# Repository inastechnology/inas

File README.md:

# INAS

Japanese documentation: [docs/jp/README.md](docs/jp/README.md)

INAS is an agriculture platform for observing field conditions, operating
irrigation equipment, managing device settings and firmware, and recording the
results of farm work. This monorepo contains the complete platform: ESP32-S3
device firmware, the Local Hub, the field-side Edge Gateway, the shared Cloud
Hub, common contracts, extensions, and user documentation.

The system is designed to keep MQTT communication and safety-critical device
operation on the field LAN. A site can operate devices directly from a Local
Hub or use an Edge Gateway that synchronizes with one parent Local Hub or Cloud
Hub over outbound HTTPS.

Start with [INAS System Specification](docs/SYSTEM_SPECIFICATION.md) for the cross-project
architecture, device roles, field data model, OTA flow, and Cloudflare hosted
options. The draw.io source for the system diagrams is
[docs/assets/inas_system_diagrams.drawio](docs/assets/inas_system_diagrams.drawio).
Documentation writing and localization rules are defined in
[docs/DOCUMENTATION_GUIDE.md](docs/DOCUMENTATION_GUIDE.md).
System-wide layer boundaries are defined in
[docs/ARCHITECTURE_LAYERING_POLICY.md](docs/ARCHITECTURE_LAYERING_POLICY.md).
Planned and community-proposed work is indexed in
[docs/FUTURE_FEATURES.md](docs/FUTURE_FEATURES.md).
Japanese documentation is stored under documentation directories such as
[docs/jp/README.md](docs/jp/README.md), [hub/doc/jp/README.md](hub/doc/jp/README.md),
and [client-devices/docs/jp/README.md](client-devices/docs/jp/README.md).

## System overview

```text
INAS devices -- MQTT --> Local Hub

INAS devices -- MQTT --> Edge Gateway -- Sync v1 HTTPS --> Local Hub or Cloud Hub
```

The Hub combines device status, measurements, irrigation history, field and
crop context, work records, Runtime Config, and OTA updates in one operator
interface. See the
[INAS System Specification](docs/SYSTEM_SPECIFICATION.md) for the complete
architecture, data flow, device roles, storage boundaries, and current feature
scope.

## Repository layout

| Path | Purpose |
|---|---|
| [`hub/`](hub/README.md) | Local Hub: Flask UI/API, MQTT processing, scheduling, storage integration, and OTA delivery |
| [`hub-cloud/`](hub-cloud/README.md) | Shared Cloudflare Workers Cloud Hub with authenticated tenant routing and one database per customer |
| [`edge-gateway/`](edge-gateway/README.md) | Field appliance: local MQTT broker integration, configuration cache, durable outbox, and parent synchronization |
| [`client-devices/`](client-devices/README.md) | PlatformIO firmware for WTR, WRS, FGT, SOI, and ENV devices, plus the shared firmware library |
| [`shared/`](shared/README.md) | Language-neutral Sync contracts and the Python edge runtime shared by the Hub and Gateway |
| [`extensions/`](extensions/README.md) | Declarative, build-time Hub UI extensions |
| [`docs-site/`](docs-site/README.md) | Japanese-first public setup, operation, and troubleshooting website |
| [`docs/`](docs/README.md) | Cross-project specifications, architecture policies, and editable system diagrams |
| [`lp/`](lp/README.md) | Product landing page and its deployable assets |
| [`pitch-deck/`](pitch-deck/) | Product presentation sources and generated artifacts |

## Installation and first run

This is a multi-component repository; there is no repository-wide installer.
Install dependencies from the directory of the component you intend to run.

### Prerequisites

- Git
- Python 3.11 or later and
  [uv](https://docs.astral.sh/uv/getting-started/installation/) for the Local
  Hub, Edge Gateway, and shared Python runtime
- Node.js 22 and npm for the Cloud Hub, admin UI, documentation site, and
  product web assets
- Linux or WSL2, GNU Make, and PlatformIO for client firmware builds

Client firmware uses symbolic links for local PlatformIO libraries. Native
Windows firmware builds are not supported; use WSL2 and clone the repository
inside the Linux filesystem rather than under `/mnt/c`.

### Clone the repository

```bash
git clone https://github.com/inastechnology/inas.git
cd inas
```

### Run the Local Hub

```bash
cd hub
uv sync
uv run ina-hub install
uv run python src/ina_device_hub/serve.py
```

The default local URL is `http://localhost:39151`. The installation command
creates the Hub environment configuration interactively. MQTT, database,
object storage, Cloudflare, and production service settings are documented in
the [Hub README](hub/README.md) and
[Hub operations documentation](hub/doc/OPERATIONS.md).

### Build client firmware

The following example builds the WTR watering device:

```bash
cd client-devices/watering-device
cp default.env.user.ini .env.user.ini
make build
```

Run `make upload` to flash a connected development device or
`make merged-bin` to produce a distributable image. Hardware preparation,
wiring, per-device build targets, and manufacturing steps are indexed from the
[client device documentation](client-devices/README.md).

### Start another component

| Goal | Initial dependency command | Detailed guide |
|---|---|---|
| Develop the Edge Gateway | `cd edge-gateway && uv sync --frozen` | [Edge Gateway README](edge-gateway/README.md) |
| Develop or test the Cloud Hub | `cd hub-cloud && npm ci` | [Cloud Hub README](hub-cloud/README.md) |
| Preview the public documentation | `cd docs-site && npm ci && npm run dev` | [Documentation site README](docs-site/README.md) |
| Build the Hub admin UI | `cd hub/admin-ui && npm ci && npm run build` | [Hub README](hub/README.md) |

## Documentation

For installation, configuration, daily operation, firmware updates, and
troubleshooting, start with the task-oriented
[INAS user documentation](https://docs.inas-technologies.com/). Its source and
local preview instructions are in [`docs-site/`](docs-site/README.md).

Developers should use these entry points instead of adding implementation
details to this README:

- [System specification](docs/SYSTEM_SPECIFICATION.md)
- [Architecture layering policy](docs/ARCHITECTURE_LAYERING_POLICY.md)
- [Device Definition specification](docs/DEVICE_DEFINITION_SPECIFICATION.md)
- [Hub Extension specification](docs/EXTENSION_SPECIFICATION.md)
- [Edge Gateway hardware and identity](docs/EDGE_GATEWAY_HARDWARE_AND_IDENTITY.md)
- [Documentation index](docs/README.md)

Each component owns its dependencies, environment variables, tests, deployment
procedures, and security notes. Run commands from that component's directory
and follow its README before changing or deploying it. Never commit real
database tokens, MQTT credentials, Cloudflare secrets, device credentials, or
generated production configuration.

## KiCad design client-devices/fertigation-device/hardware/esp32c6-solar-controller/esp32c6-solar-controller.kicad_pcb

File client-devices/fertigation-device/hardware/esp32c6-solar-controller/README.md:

# FGT ESP32-C6 Solar Controller

Status: **development CAD only — not fabricated and not used by the current
FGT hardware**.

This directory contains an in-progress candidate design for a future dedicated
controller PCB. A physical board based on this design does not currently exist,
has not been assembled or electrically validated, and must not be treated as
the current FGT wiring or firmware pin contract. Generated ERC/DRC, Gerber,
BOM, CPL, and enclosure outputs show CAD consistency only; they are not evidence
of a manufactured or working device.

The current FGT firmware bring-up uses the direct-wired XIAO ESP32-C6 pin
contract in
[`../../docs/jp/minimal_wiring.md`](../../docs/jp/minimal_wiring.md).

## Design documents

- [BOM index](BOM_DRAFT.md)
- [Rev A 試作発注・組立ガイド](ORDERING.md)
- [主要部品の選定結果](PART_SELECTION.md) — 採用MPN、LCSC番号、定格根拠、
  ヒューズとコネクタの組み合わせ、発注前確認条件
- [部品仕様調査](COMPONENT_SPECIFICATIONS.md) — メーカー一次資料に基づく
  採用部品ごとの電気仕様、pinout、回路上の使用条件
- [Rev A 電気設計DR](ELECTRICAL_DESIGN_REVIEW.md) — 仕様照合結果、回路計算、
  今回の修正、試作後に必要な安全・熱・負荷試験
- [Electrical BOM](ELECTRICAL_BOM.md) — PCB実装部品、電源、RS485、
  MOSFET出力回路、基板上コネクタ
- [Electrical procurement worksheet](ELECTRICAL_PROCUREMENT.csv) —
  主要電子部品の仕様、メーカー型番、LCSC番号、一次資料、実装区分
- [Enclosure and assembly BOM](ENCLOSURE_BOM.md) — 防水筐体、外部コネクタ、
  ハーネス、取付金具、ラベル、シール材
- [Hydraulic and field BOM](HYDRAULIC_AND_FIELD_BOM.md) — 液肥タンク、
  ポンプ、配管、液面・漏水検知、水中コネクタの適用条件
- [Hydraulic procurement worksheet](HYDRAULIC_AND_FIELD_PROCUREMENT.csv) —
  メーカー、型番、購入先URL、単価、発注数の記入用CSV

## KiCad development design

Open [esp32c6-solar-controller.kicad_pro](esp32c6-solar-controller.kicad_pro)
with KiCad 10. The project contains the Rev A single-sheet A1 schematic and routed
`180 x 115 mm` four-layer PCB:

- 20 A shared 12 V input path with LM74610-Q1 reverse-polarity control;
- XIAO ESP32-C6 direct-GPIO control section;
- one board-mounted THVD1410DR RS485 interface with termination and TVS;
- PTC-protected 12 V field power and three generic parallel RS485 connectors;
- normally-closed leak and emergency-stop safety inputs;
- reset-safe hardware gate permission; and
- five individually fused low-side MOSFET output channels.

Related project files:

- [KiCad schematic](esp32c6-solar-controller.kicad_sch)
- [Local symbol library](INA.kicad_sym)
- [XIAO 24-pad SMD footprint](INA_ESP32C6.pretty/XIAO_ESP32C6_SMD_24P.kicad_mod)
- [Schematic PDF](exports/esp32c6-solar-controller.pdf)
- [Schematic layout preview](exports/review/schematic-a1-layout.png)
- [PCB top render](exports/review/pcb-top.png)
- [PCB isometric render](exports/review/pcb-isometric.png)
- [JLCPCB Gerber ZIP](exports/esp32c6-solar-controller-rev-a-gerbers.zip)
- [JLCPCB SMT BOM](exports/assembly/jlcpcb-smt-bom.csv)
- [JLCPCB SMT CPL](exports/assembly/jlcpcb-smt-cpl.csv)
- [Post-assembly BOM](exports/assembly/post-assembly-bom.csv)
- [Board-only STEP](exports/mechanical/controller-board-only-rev-a.step)
- [Final ERC](exports/erc-final.json)
- [Final DRC](exports/drc-final.json)
- [Connectivity netlist](exports/esp32c6-solar-controller.net.xml)

The schematic, local libraries, and release outputs are reproducible with:

```bash
python3 tools/generate_schematic.py
tools/export_release.sh
```

Running the generator overwrites the generated KiCad schematic, project,
symbol library, and XIAO footprint. Do not make GUI-only schematic edits and
then rerun the generator without first carrying those changes back into the
generator.

Validation status:

- opened and exported with KiCad CLI 10.0.5;
- ERC: zero errors and zero warnings;
- PCB DRC: zero violations and zero unconnected items;
- 121 schematic components and 72 named nets;
- 125 PCB footprints including four mounting holes and 72 PCB nets;
- 90 JLCPCB top-side SMT placements, 23 post-assembly parts, and 8 explicit
  DNP parts;
- every populated SMT part has MPN, footprint, and LCSC number; and
- PDF, Gerber, drill, BOM/CPL, assembly, DXF, SVG, and STEP exports generated.

The project-local symbols currently use passive electrical pin types. ERC
therefore verifies file integrity, grid placement, named connectivity,
unconnected-pin declarations, and library consistency, but it does not replace
an electrical review of driver direction, power-source conflicts, current
ratings, or fail-safe behavior.

Major active parts, power semiconductors, fuses, connector families, and
manufacturer land patterns are fixed in [PART_SELECTION.md](PART_SELECTION.md).
JLCPCB/LCSC stock, placement rotation, and package data are still checked in the
order preview. Charger voltage, actual motor inrush, enclosure temperature, and
field wiring are commissioning limits rather than reasons to leave the PCB
undefined.

## Product boundary

This CAD is a candidate future `FGT` hardware profile for a solar-powered
fertilizer mixing and irrigation controller. It is not the current prototype
hardware profile. If developed further, it is intended to keep the existing
FGT state machine, Runtime Config, status contract, and safety invariants while
using a directly soldered Seeed Studio XIAO ESP32-C6.
The module uses the official 24-pad SMD land pattern so its four underside GPIO
pads are available. The XIAO is consequently a reflow/hot-air service part
rather than a socket-replaceable module.

The physical board exposes five generic MOSFET outputs, one RS485 bus on three
parallel terminals, one flow-pulse input, and four contact inputs. The current
FGT Runtime Config maps those generic resources to:

- clean-water inlet valve or transfer pump;
- A concentrate dosing pump;
- B concentrate dosing pump;
- mixing/circulation pump;
- irrigation pump;
- inlet flow pulse;
- tank-empty and tank-full switches;
- leak and emergency-stop inputs; and
- RS485 devices selected for each installation.

No soil, PAR, or other sensor type is fixed in the PCB, connector name, or
electrical BOM. Device model, Modbus address, register map, and meaning belong
to deployment configuration and firmware/device-definition data.

The solar charger, battery BMS, main fuse, and battery disconnect are external
assemblies. The first enclosure may hold the off-board solar controller and
provide separate two-pin panel connectors for the solar panel and battery. The
controller PCB receives power only from the solar controller's protected load
output. This PCB does not charge an unknown battery chemistry.

## Prototype architecture

```text
solar panel -- 2-pin panel connector --+
                                        |
                                off-board solar controller
                                        |
battery ----- 2-pin panel connector ----+
                                        |
                                 protected LOAD output
                                        |
    +-- protected board input -----------------------------+
    |                                                      |
    +-- 12 V actuator distribution (optional 5V_ACT)       |
                                                           |
                              +----------------------------+
                              |
                     reverse-polarity protection
                              |
                +-------------+-------------------+
                |                                 |
           5 V logic buck                 PTC-protected 12 V field rail
                |                                 |
        XIAO ESP32-C6 direct GPIO         generic RS485 ports 1 / 2 / 3
                |
        safety-gated driver enables
                |
       five replaceable actuator drivers
```

The controller board repeats one safety-gated MOSFET channel per actuator.
Power-SMT MOSFETs, gate drivers, fuses, suppression devices, and connectors are
selected only after the real load voltage, running current, stall current, and
inrush measurements are approved. Revision 1 keeps each power channel
independently fused and testable instead of hiding it in a sealed power module.

## XIAO ESP32-C6 pin contract

| Function | XIAO pad | ESP32-C6 GPIO | Reset/safety rule |
|---|---|---:|---|
| Battery voltage ADC | `D0` / pad 1 | `GPIO0` | High-impedance divider; never exceed 3.3 V |
| Output command 1 | `D1` / pad 2 | `GPIO1` | External 47 kohm pull-down; boot default OFF |
| Inlet flow pulse | `D2` / pad 3 | `GPIO2` | Filtered input with defined pull state |
| Actuator master enable | `D3` / pad 4 | `GPIO21` | External pull-down; LOW disables all outputs |
| Output command 2 | `D4` / pad 5 | `GPIO22` | External 47 kohm pull-down; boot default OFF |
| Output command 3 | `D5` / pad 6 | `GPIO23` | External 47 kohm pull-down; boot default OFF |
| RS485 TX | `D6` / pad 7 | `GPIO16` | Direct 3.3 V UART connection |
| RS485 RX | `D7` / pad 8 | `GPIO17` | 3.3 V logic only |
| RS485 DE/RE | `D8` / pad 9 | `GPIO19` | External pull-down selects receive mode |
| Tank empty | `D9` / pad 10 | `GPIO20` | Filtered active-low input |
| Tank full | `D10` / pad 11 | `GPIO18` | Filtered active-low input |
| Output command 4 | `MTDI` / pad 15 | `GPIO5` | Strap pin held LOW by 47 kohm output pull-down |
| Leak status | `MTDO` / pad 16 | `GPIO7` | Filtered status input; hardware also removes permission |
| Output command 5 | `MTMS` / pad 19 | `GPIO4` | Strap pin held LOW by 47 kohm output pull-down |
| Emergency-stop status | `MTCK` / pad 20 | `GPIO6` | Filtered status input; hardware also removes permission |

The XIAO USB-C connector, BOOT button, and RESET button remain accessible after
installation. The XIAO antenna end must be located at a board and enclosure
edge, with no copper, battery, pump, cable bundle, or metal hardware in its
antenna keep-out region.

`GPIO4` and `GPIO5` are ESP32-C6 strapping pins sampled during reset. They are
used only for output commands because each one has a physical 47 kohm
pull-down, producing the required OFF/LOW boot state. They must never receive
an external pull-up. Production validation must include cold boot, reset, USB
download, and OTA restart tests with all five gates verified OFF.

The five direct commands retain the FGT default order: clean-water inlet,
A concentrate, B concentrate, mixer, and irrigation. They reach the gate
drivers only when the independent master-enable safety chain is valid.

Leak and emergency stop must also remove actuator permission in hardware. The
firmware reads and reports the same signals directly, but a crashed MCU or
incorrect output command cannot override the hardware disable.

This PCB requires a direct-GPIO firmware hardware profile matching the table
above.

## Implemented electrical sections

1. **Power input**
   - keyed battery connector;
   - replaceable board fuse;
   - reverse-polarity protection;
   - input TVS selected after the maximum charger voltage is known;
   - service power switch connector;
   - battery voltage divider with ADC protection;
   - 5 V buck sized for XIAO, RS485, control logic, and margin.
2. **Controller**
   - directly soldered XIAO ESP32-C6 using the official 24-pad SMD pattern;
   - accessible USB-C, BOOT, and RESET;
   - reset-safe pull-downs.
3. **Safety and I/O**
   - direct MCU GPIO for five commands and four contact inputs;
   - filtered dry-contact inputs;
   - hardware master-enable chain;
   - five fused generic 12 V low-side MOSFET outputs;
   - flow pulse input.
4. **RS485 field bus**
   - one board-mounted TI THVD1410DR 3.3 V, 500 kbps half-duplex transceiver
     for the complete bus;
   - SOIC-8 package for JLCPCB SMT assembly and prototype rework;
   - bus TVS and connector-side protection;
   - selectable 120 ohm termination;
   - optional bias footprints;
   - PTC-protected, non-switched 12 V field supply;
   - three parallel, numbered connectors carrying `A`, `B`, `GND`, and `12V`.
5. **Connectors and mechanical**
   - terminal labels identical to Hub output inventory;
   - mounting holes and keep-outs;
   - enclosure and cable-gland datum locations.

## Proposed external connectors

| Ref | Label | Signals |
|---|---|---|
| `J1` | `POWER FROM CHARGER LOAD` | `LOAD+`, `LOAD-` |
| `J2` | `RS485 PORT 1` | `12V_FIELD`, `GND`, `A`, `B` |
| `J3` | `RS485 PORT 2` | `12V_FIELD`, `GND`, `A`, `B` |
| `J4` | `RS485 PORT 3` | `12V_FIELD`, `GND`, `A`, `B` |
| `J5` | `FLOW` | sensor supply, `FLOW_PULSE`, `GND` |
| `J6` | `TANK EMPTY` | contact, common |
| `J7` | `TANK FULL` | contact, common |
| `J8` | `LEAK` | contact, common |
| `J9` | `EMERGENCY STOP` | normally-closed safety loop |
| `J10` | `MOSFET OUT 1` | `12V_ACT`, switched return |
| `J11` | `MOSFET OUT 2` | `12V_ACT`, switched return |
| `J12` | `MOSFET OUT 3` | `12V_ACT`, switched return |
| `J13` | `MOSFET OUT 4` | `12V_ACT`, switched return |
| `J14` | `MOSFET OUT 5` | `12V_ACT`, switched return |

The three RS485 connectors share one UART, one transceiver, and one A/B trunk;
they are connection points on one bus, not three independent interfaces.
Connected devices must use non-conflicting addresses and compatible serial
settings. Only the two physical ends of the trunk are terminated; a 120 ohm
resistor is not fitted at every connector. Keep stubs short and prefer a
daisy-chain cable layout for long field wiring.

`12V_FIELD` is protected by a shared 0.75 A hold PTC but is not switched or
assigned to a particular sensor. A device that requires power cycling can be
wired through one of the generic MOSFET outputs, subject to its voltage,
polarity, flyback, and current requirements.

Each MOSFET connector carries 12 V positive and a low-side switched return.
The PCB has no pump or valve function printed into these five channels. Each
direct DC load must be below 100 W, corresponding to less than 8.33 A running
current at 12 V. The channel design target is 10 A continuous after thermal
derating; startup and locked-rotor current remain separate verification items.

The candidate PCB mapping is:

| Physical output | Runtime role |
|---|---|
| `MOSFET OUT 1` | Clean-water inlet |
| `MOSFET OUT 2` | A concentrate pump |
| `MOSFET OUT 3` | B concentrate pump |
| `MOSFET OUT 4` | Mixer |
| `MOSFET OUT 5` | Irrigation pump |

Normal operation energizes one 12 V MOSFET channel. The absolute interlock
limit is two channels, so the maximum steady load is below 200 W or about
16.7 A at 12 V. The shared input path targets 20 A continuous after thermal
derating, and its Phoenix PC 5 connector is rated 32 A nominal.

The initial two-channel exceptions are `A PUMP + MIXER` and
`B PUMP + MIXER`. `A PUMP + B PUMP` is always forbidden. Two motors are never
started simultaneously; the second channel may start only after the first
channel's inrush interval. Any other pair requires an explicitly reviewed
sequence. A request for a third active channel is rejected and treated as a
fault.

The footprint may support a future `5V_ACT` rail, but it is separate from
`5V_LOGIC`. Each channel uses a high-current through-hole assembly link between
`OUTx+` and either `12V_ACT` or optional `5V_ACT`. The link is soldered during
assembly, is not accessible from outside the enclosure, and its voltage is
printed on the terminal label. Do not pass pump current through a 2.54 mm
configuration jumper, and never connect a pump to the XIAO logic supply.

## PCB and enclosure baseline

- Four-layer PCB: signal / solid ground / power / signal.
- JLCPCB mixed-technology PCBA is the manufacturing baseline.
- Logic, RS485, protection, gate drivers, and power MOSFETs use top-side SMT
  where practical; high-current terminals and serviceable fuses may use
  JLCPCB-supported THT/wave assembly.
- KiCad properties retain manufacturer and JLCPCB/LCSC part numbers, and the
  release package includes matching JLCPCB BOM and CPL files.
- Pluggable terminal blocks at the enclosure cable-entry edge.
- XIAO antenna and USB at the opposite edge.
- Logic and RS485 separated from pump wiring and driver heat.
- Four mounting holes outside the XIAO antenna keep-out.
- Released board outline: 180 mm x 115 mm with four M3 holes on
  172 mm x 107 mm pitch. This is approximately 33% less board area than the
  superseded 220 mm x 140 mm layout while preserving connector service space.
- Baseline enclosure: Takachi `BCPR304012S`, IP65 polycarbonate box with outdoor
  roof, and `BMP3040Z` 265 mm x 365 mm internal mounting plate.
- The reference off-board solar controller image is approximately
  134 mm x 70 mm, with approximately 126 mm x 50 mm mounting-hole spacing.
  If it is mounted inside the same enclosure, reserve a separate mounting area
  and finger clearance for all six screw terminals.
- Enclosure CAD is produced separately from KiCad and references the PCB STEP
  export, terminal heights, USB service clearance, and cable-gland locations.

## Required safety behavior

- All actuator outputs are OFF at boot, reset, OTA, sleep, missing controller,
  and invalid configuration.
- A and B cannot be active together.
- A or B requires mixing to be active.
- Water inlet and irrigation cannot be active together.
- Emergency stop and leak remove driver permission without firmware action.
- The PTC-protected RS485 field rail cannot remove power from the controller.
- A failed or disconnected RS485 device is reported according to its configured
  device definition and cannot silently approve unattended fertilizer dosing.
- Interrupted batches never resume automatically.
- The first fertilizer run follows successful water-only tests and measured
  pump/flow calibration.

## Required measurements before field commissioning

If a future PCB is fabricated from this CAD, it can remain sensor-model
independent because the RS485 and MOSFET ports are generic. The following
values must be measured before that future board is connected to real loads,
fertilizer, or unattended outdoor operation:

1. Battery chemistry and configuration:
   - 4S LiFePO4, 12 V lead-acid, 3S Li-ion, or another pack;
   - normal operating range;
   - maximum charger voltage;
   - BMS continuous and peak current.
2. Solar panel and external charge-controller model.
3. For each of the five actuators:
   - model number;
   - nominal voltage;
   - running current;
   - startup or stall current;
   - whether the input is a dry-contact/logic enable or a direct DC load.
   - all five currently planned pumps are 12 V and below 100 W;
   - confirm measured current, inrush, and polarity before selecting the shared
     12 V power stage;
   - normal operation permits one active channel;
   - the absolute limit is two active channels, initially only
     `A PUMP + MIXER` or `B PUMP + MIXER`;
   - simultaneous motor starts and `A PUMP + B PUMP` are prohibited.
4. Flow sensor model, supply voltage, and pulse output type.
5. Tank-empty, tank-full, leak, and emergency-stop contact types and cable
   lengths.
6. Expected RS485 bus length, device count, baud rate, address plan, and cable
   type. Individual device models remain deployment configuration rather than
   PCB assumptions.
7. Required enclosure rating, mounting method, connector direction, and
   preferred off-the-shelf enclosure.
8. RS485 grounding/shielding strategy and whether field conditions require
   galvanic isolation.

## Official design references

- Seeed Studio XIAO ESP32-C6 pin map and power notes:
  <https://wiki.seeedstudio.com/xiao_esp32c6_getting_started/>
- Seeed Studio official XIAO KiCad footprint archive:
  <https://files.seeedstudio.com/wiki/XIAO-KiCad-Library/New_XIAO_Series_Footprints.zip>
- Espressif ESP32-C6 GPIO and strapping-pin notes:
  <https://docs.espressif.com/projects/esp-idf/en/stable/esp32c6/api-reference/peripherals/gpio.html>
- Espressif ESP32-C6 hardware design guidelines:
  <https://docs.espressif.com/projects/esp-hardware-design-guidelines/en/latest/esp32c6/index.html>
- TI THVD1410 product page and datasheet:
  <https://www.ti.com/product/THVD1410>
- JLCPCB KiCad 10 BOM/CPL export guidance:
  <https://jlcpcb.com/help/article/how-to-generate-the-bom-and-centroid-file-from-kicad>
- JLCPCB mixed SMT/THT assembly FAQ:
  <https://jlcpcb.com/help/article/pcb-assembly-faqs>
- Existing FGT requirements:
  [../../docs/requirements.md](../../docs/requirements.md)
- Existing FGT hardware and power contract:
  [../../docs/hardware_and_power.md](../../docs/hardware_and_power.md)
- Existing FGT verification plan:
  [../../docs/verification_plan.md](../../docs/verification_plan.md)

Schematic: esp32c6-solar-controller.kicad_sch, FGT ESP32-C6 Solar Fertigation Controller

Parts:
C1: 470u 35V LOW-ESR; CP_Radial_D10.0mm_P5.00mm; MPN UHE1V471MPD; LCSC C116237
C2, C9, C10: 22u 10V X7R; C_1206_3216Metric; MPN CL31B226KPHNNNE; LCSC C87996
C3, C5, C7, C12, C20, C21, C22, C23, C24, C30, C31, C32, C33, C34: 100n 50V X7R; C_0603_1608Metric; MPN CL10B104KB8NNNC; LCSC C1591
C6, C35, C36, C37: 2.2u 16V X7R; C_0805_2012Metric; MPN CL21B225KOFNNNE; LCSC C28234
C8: 10u 50V X7R; C_1206_3216Metric; MPN CL31B106KBHNNNE; LCSC C89632
C11: 47u 25V LOW-ESR; CP_Radial_D5.0mm_P2.00mm; MPN UHE1E470MDD; LCSC C134230
C13: 100p 50V C0G; C_0603_1608Metric; MPN CL10C101JB8NNNC; LCSC C14858
D1: SMBJ18A; D_SMB; MPN SMBJ18A; LCSC C151256
D2: CDSOT23-SM712; SOT-23; MPN CDSOT23-SM712; LCSC C404012
D3: BAT54S,215 ADC CLAMP; SOT-23; MPN BAT54S,215; LCSC C47546
D10, D11, D12, D13, D14: STPS30SM60SG-TR 60V/30A; TO-263-2_TabPin1; MPN STPS30SM60SG-TR; LCSC C2935135
D20, D21, D22, D23, D24: OUTPUT TVS/SNUBBER DNP; D_SMB; not fitted
D30, D31, D32, D33, D34: TPD1E10B06DPYR; X1SON-2_L1.0-W0.6-P0.65-BI-1; MPN TPD1E10B06DPYR; LCSC C48260
F1: ATO HOLDER + 20A FUSE; 178.6165.0001; MPN 178.6165.0001 + 0287020.H; LCSC C207060
F2: 0.75A HOLD PTC; Fuse_1206_3216Metric; MPN MF-NSMF075-2; LCSC C89653
F3: 0.75A HOLD / 24V PTC; Fuse_1812_4532Metric; MPN MF-MSMF075/24-2; LCSC C208467
F10: MOSFET OUT 1 ATO HOLDER + 10A FUSE; 178.6165.0001; MPN 178.6165.0001 + 0287010.H; LCSC C207060
F11: MOSFET OUT 2 ATO HOLDER + 10A FUSE; 178.6165.0001; MPN 178.6165.0001 + 0287010.H; LCSC C207060
F12: MOSFET OUT 3 ATO HOLDER + 10A FUSE; 178.6165.0001; MPN 178.6165.0001 + 0287010.H; LCSC C207060
F13: MOSFET OUT 4 ATO HOLDER + 10A FUSE; 178.6165.0001; MPN 178.6165.0001 + 0287010.H; LCSC C207060
F14: MOSFET OUT 5 ATO HOLDER + 10A FUSE; 178.6165.0001; MPN 178.6165.0001 + 0287010.H; LCSC C207060
J1: PC 5/2-G-7.62 POWER INPUT; Phoenix_PC5_2_G_7_62_1720466; MPN 1720466
J2: RS485 PORT 1; Phoenix_MSTBA_2_5_4_G_5_08_1757268; MPN 1757268
J3: RS485 PORT 2; Phoenix_MSTBA_2_5_4_G_5_08_1757268; MPN 1757268
J4: RS485 PORT 3; Phoenix_MSTBA_2_5_4_G_5_08_1757268; MPN 1757268; not fitted
J5: FLOW 12V/PULSE/GND; Phoenix_MSTBA_2_5_3_G_5_08_1757255; MPN 1757255
J6: TANK EMPTY; Phoenix_MSTBA_2_5_2_G_5_08_1757242; MPN 1757242
J7: TANK FULL; Phoenix_MSTBA_2_5_2_G_5_08_1757242; MPN 1757242
J8: LEAK NC; Phoenix_MSTBA_2_5_2_G_5_08_1757242; MPN 1757242
J9: EMERGENCY STOP NC; Phoenix_MSTBA_2_5_2_G_5_08_1757242; MPN 1757242
J10: MOSFET OUT 1 12V; Phoenix_PC5_2_G_7_62_1720466; MPN 1720466
J11: MOSFET OUT 2 12V; Phoenix_PC5_2_G_7_62_1720466; MPN 1720466
J12: MOSFET OUT 3 12V; Phoenix_PC5_2_G_7_62_1720466; MPN 1720466
J13: MOSFET OUT 4 12V; Phoenix_PC5_2_G_7_62_1720466; MPN 1720466
J14: MOSFET OUT 5 12V; Phoenix_PC5_2_G_7_62_1720466; MPN 1720466
JP1: RS485 TERM ENABLE; PinHeader_1x02_P2.54mm_Vertical; MPN PRPC002SAAN-RC; LCSC C3346540
L1: 4.7uH 4.6A; L_Bourns_SRP5030T; MPN SRP5030TA-4R7M; LCSC C2047088
Q1, Q2, Q3, Q4, Q5, Q6: CSD18540Q5B 60V; VSON-CLIP-8_L5.0-W6.0-P1.27-BL; MPN CSD18540Q5B; LCSC C86513
R1: 150k 1%; R_0603_1608Metric; MPN 0603WAF1503T5E; LCSC C22807
R2: 27k 1%; R_0603_1608Metric; MPN 0603WAF2702T5E; LCSC C22967
R3, R20, R22, R24, R26: 1k 1%; R_0603_1608Metric; MPN 0603WAF1001T5E; LCSC C21190
R8, R9, R18, R19, R40, R41, R42, R43, R44, R55, R56, R57, R58, R59: 47k 1%; R_0603_1608Metric; MPN 0603WAF4702T5E; LCSC C25819
R10, R11: 10R 1%; R_0603_1608Metric; MPN 0603WAF100JT5E; LCSC C22859
R12: 120R 1%; R_0805_2012Metric; MPN 0805W8F1200T5E; LCSC C17437
R13, R14: 680R 1% BIAS; R_0603_1608Metric; MPN 0603WAF6800T5E; LCSC C23228; not fitted
R16, R21, R23, R25, R27: 10k 1%; R_0603_1608Metric; MPN 0603WAF1002T5E; LCSC C25804
R17: 2.2k 1%; R_0603_1608Metric; MPN 0603WAF2201T5E; LCSC C4190
R50, R51, R52, R53, R54: 22R 1%; R_0603_1608Metric; MPN 0603WAF220JT5E; LCSC C23345
U1: Seeed XIAO ESP32-C6 SMD; XIAO_ESP32C6_SMD_24P; MPN XIAO ESP32-C6
U3: THVD1410DR; SOIC-8_3.9x4.9mm_P1.27mm; MPN THVD1410DR; LCSC C2671345
U4: AP63205WU-7 5V/2A; TSOT-23-6; MPN AP63205WU-7; LCSC C2071056
U5, U6: SN74AHCT08DR; SOIC-14_3.9x8.7mm_P1.27mm; MPN SN74AHCT08DR; LCSC C7480
U7, U8, U9: TC4427AEOA; SOIC-8_3.9x4.9mm_P1.27mm; MPN TC4427AEOA; LCSC C18690
U11: SN74HC14DR; SOIC-14_3.9x8.7mm_P1.27mm; MPN SN74HC14DR; LCSC C6820
U12: TLV7031DBVR; SOT-23-5; MPN TLV7031DBVR; LCSC C2869832
U13: LM74610QDGKRQ1; VSSOP-8_L3.0-W3.0-P0.65-LS5.0-BL; MPN LM74610QDGKRQ1; LCSC C2649431

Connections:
3V3: C5.1, C24.1, D3.2 (K2_3V3), R13.1, R16.1, R18.1, R21.1, R23.1, R25.1, R27.1, U1.12 (3V3), U1.22 (3V3), U3.8 (VCC), U11.14 (VCC), U12.5 (VCC)
5V_LOGIC: C2.1, C30.1, C31.1, C32.1, C33.1, C34.1, C35.1, C36.1, C37.1, F2.2 (OUT), U1.14 (5V), U5.14 (VCC), U6.14 (VCC), U7.6 (VDD), U8.6 (VDD), U9.6 (VDD)
5V_RAW: C9.1, C10.1, F2.1 (IN), L1.2, U4.1 (FB)
12V_ACT: C1.1, C8.1, C13.2, D1.1 (K), F3.1 (IN), F10.1 (IN), F11.1 (IN), F12.1 (IN), F13.1 (IN), F14.1 (IN), Q1.2 (D), R1.1, U4.2 (EN), U4.3 (VIN), U13.8 (CATHODE)
12V_FIELD: C11.1, F3.2 (OUT), J2.1 (PIN1), J3.1 (PIN1), J4.1 (PIN1), J5.1 (PIN1)
BATT_ADC: C3.1, D3.3 (K1_A2_ADC), R3.2, U1.1 (D0_GPIO0)
BATT_DIV: R1.2, R2.1, R3.1
BUCK_BST: C7.1, U4.6 (BST)
BUCK_SW: C7.2, L1.1, U4.5 (SW)
DRIVER1: R50.1, U7.7 (OUTA)
DRIVER2: R51.1, U7.5 (OUTB)
DRIVER3: R52.1, U8.7 (OUTA)
DRIVER4: R53.1, U8.5 (OUTB)
DRIVER5: R54.1, U9.7 (OUTA)
EMPTY_FIELD: D30.1 (IO), J6.1 (PIN1), R20.1
EMPTY_RAW: C20.1, R20.2, R21.2, U11.1 (1A)
ESTOP_FIELD: D33.1 (IO), J9.1 (PIN1), R26.1
ESTOP_OK: U1.20 (MTCK_GPIO6), U5.5 (2B), U11.8 (4Y)
ESTOP_RAW: C23.1, R26.2, R27.2, U11.9 (4A)
FLOW_FIELD: D34.1 (IO), J5.2 (PIN2), R16.2, R17.1
FLOW_PULSE: U1.3 (D2_GPIO2), U12.1 (OUT)
FLOW_REF: R18.2, R19.1, U12.4 (IN-)
FLOW_SENSE: C12.1, R17.2, U12.3 (IN+)
FULL_FIELD: D31.1 (IO), J7.1 (PIN1), R22.1
FULL_RAW: C21.1, R22.2, R23.2, U11.3 (2A)
GATE1: Q2.1 (G), R50.2, R55.1
GATE2: Q3.1 (G), R51.2, R56.1
GATE3: Q4.1 (G), R52.2, R57.1
GATE4: Q5.1 (G), R53.2, R58.1
GATE5: Q6.1 (G), R54.2, R59.1
GND: C1.2, C2.2, C3.2, C5.2, C8.2, C9.2, C10.2, C11.2, C12.2, C20.2, C21.2, C22.2, C23.2, C24.2, C30.2, C31.2, C32.2, C33.2, C34.2, C35.2, C36.2, C37.2, D1.2 (A), D2.3 (COMMON), D3.1 (A1_GND), D20.2 (A), D21.2 (A), D22.2 (A), D23.2 (A), D24.2 (A), D30.2 (GND), D31.2 (GND), D32.2 (GND), D33.2 (GND), D34.2 (GND), J1.2 (PIN2), J2.2 (PIN2), J3.2 (PIN2), J4.2 (PIN2), J5.3 (PIN3), J6.2 (PIN2), J7.2 (PIN2), J8.2 (PIN2), J9.2 (PIN2), Q2.3 (S), Q3.3 (S), Q4.3 (S), Q5.3 (S), Q6.3 (S), R2.2, R8.2, R9.2, R14.2, R19.2, R40.2, R41.2, R42.2, R43.2, R44.2, R55.2, R56.2, R57.2, R58.2, R59.2, U1.13 (GND), U1.18 (GND), U1.24 (GND), U3.5 (GND), U4.4 (GND), U5.7 (GND), U6.7 (GND), U6.9 (3B), U6.10 (3A), U7.3 (GND), U8.3 (GND), U9.3 (GND), U9.4 (INB), U11.7 (GND), U11.11 (5A), U11.13 (6A), U12.2 (GND)
LEAK_FIELD: D32.1 (IO), J8.1 (PIN1), R24.1
LEAK_OK: U1.16 (MTDO_GPIO7), U5.2 (1B), U11.6 (3Y)
LEAK_RAW: C22.1, R24.2, R25.2, U11.5 (3A)
LOAD_POS: F1.1 (IN), J1.1 (PIN1)
MASTER_PERMIT: U5.6 (2Y), U5.9 (3B), U5.12 (4B), U6.2 (1B), U6.5 (2B), U6.12 (4B)
MCU_MASTER_EN: R8.1, U1.4 (D3_GPIO21), U5.1 (1A)
OUT1_POS: D10.1 (K), F10.2 (OUT), J10.1 (PIN1)
OUT1_SW: D10.2 (A), D20.1 (K), J10.2 (PIN2), Q2.2 (D)
OUT2_POS: D11.1 (K), F11.2 (OUT), J11.1 (PIN1)
OUT2_SW: D11.2 (A), D21.1 (K), J11.2 (PIN2), Q3.2 (D)
OUT3_POS: D12.1 (K), F12.2 (OUT), J12.1 (PIN1)
OUT3_SW: D12.2 (A), D22.1 (K), J12.2 (PIN2), Q4.2 (D)
OUT4_POS: D13.1 (K), F13.2 (OUT), J13.1 (PIN1)
OUT4_SW: D13.2 (A), D23.1 (K), J13.2 (PIN2), Q5.2 (D)
OUT5_POS: D14.1 (K), F14.2 (OUT), J14.1 (PIN1)
OUT5_SW: D14.2 (A), D24.1 (K), J14.2 (PIN2), Q6.2 (D)
OUT_CMD1: R40.1, U1.2 (D1_GPIO1), U5.10 (3A)
OUT_CMD2: R41.1, U1.5 (D4_GPIO22), U5.13 (4A)
OUT_CMD3: R42.1, U1.6 (D5_GPIO23), U6.1 (1A)
OUT_CMD4: R43.1, U1.15 (MTDI_GPIO5_STRAP), U6.4 (2A)
OUT_CMD5: R44.1, U1.19 (MTMS_GPIO4_STRAP), U6.13 (4A)
OUT_GATED1: U5.8 (3Y), U7.2 (INA)
OUT_GATED2: U5.11 (4Y), U7.4 (INB)
OUT_GATED3: U6.3 (1Y), U8.2 (INA)
OUT_GATED4: U6.6 (2Y), U8.4 (INB)
OUT_GATED5: U6.11 (4Y), U9.2 (INA)
RPOL_GATE: Q1.1 (G), U13.2 (GATE_PULL_DOWN), U13.6 (GATE_DRIVE)
RPOL_VCAPH: C6.1, U13.7 (VCAPH)
RPOL_VCAPL: C6.2, U13.1 (VCAPL)
RS485_A: D2.1 (LINE_A), J2.3 (PIN3), J3.3 (PIN3), J4.3 (PIN3), R10.2, R12.1, R13.2
RS485_A_LOCAL: R10.1, U3.6 (A)
RS485_B: D2.2 (LINE_B), J2.4 (PIN4), J3.4 (PIN4), J4.4 (PIN4), JP1.2, R11.2, R14.1
RS485_B_LOCAL: R11.1, U3.7 (B)
RS485_DIR: R9.1, U1.9 (D8_GPIO19_DIR), U3.2 (~RE), U3.3 (DE)
RS485_RX: U1.8 (D7_GPIO17_RX), U3.1 (R)
RS485_TX: U1.7 (D6_GPIO16_TX), U3.4 (D)
SAFETY_STAGE1: U5.3 (1Y), U5.4 (2A)
TANK_EMPTY_ACTIVE: U1.10 (D9_GPIO20), U11.2 (1Y)
TANK_FULL_ACTIVE: U1.11 (D10_GPIO18), U11.4 (2Y)
TERM_NODE: JP1.1, R12.2
VIN_FUSED: C13.1, F1.2 (OUT), Q1.3 (S), U13.4 (ANODE)

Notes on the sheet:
POWER INPUT / 20 A SHARED PATH
Normal: one 12 V output. Absolute limit: two outputs (<200 W total).
DIRECT GPIO CONTROLLER
RS485 / GENERIC PARALLEL PORTS / NO SENSOR TYPE ASSUMPTION
FIELD INPUTS / NC SAFETY LOOPS FAIL OPEN
HARD SAFETY GATING / ALL OUTPUTS DEFAULT OFF
Physical outputs are generic. Runtime mapping enforces current FGT A/B/MIXER safety rules.
Never start two motors simultaneously. Third active command is a fault.
12 V MOSFET OUTPUTS / <100 W EACH / 10 A CONTINUOUS TARGET
REV A ENGINEERING BUILD / ORDERABLE PROTOTYPE
Bench validation is mandatory before field use: charger range, inrush, current, thermal rise, faults, and wet-enclosure testing.
JLCPCB PCBA: top-side SMT preferred; connector/fuse THT assembly permitted; verify LCSC stock at release.

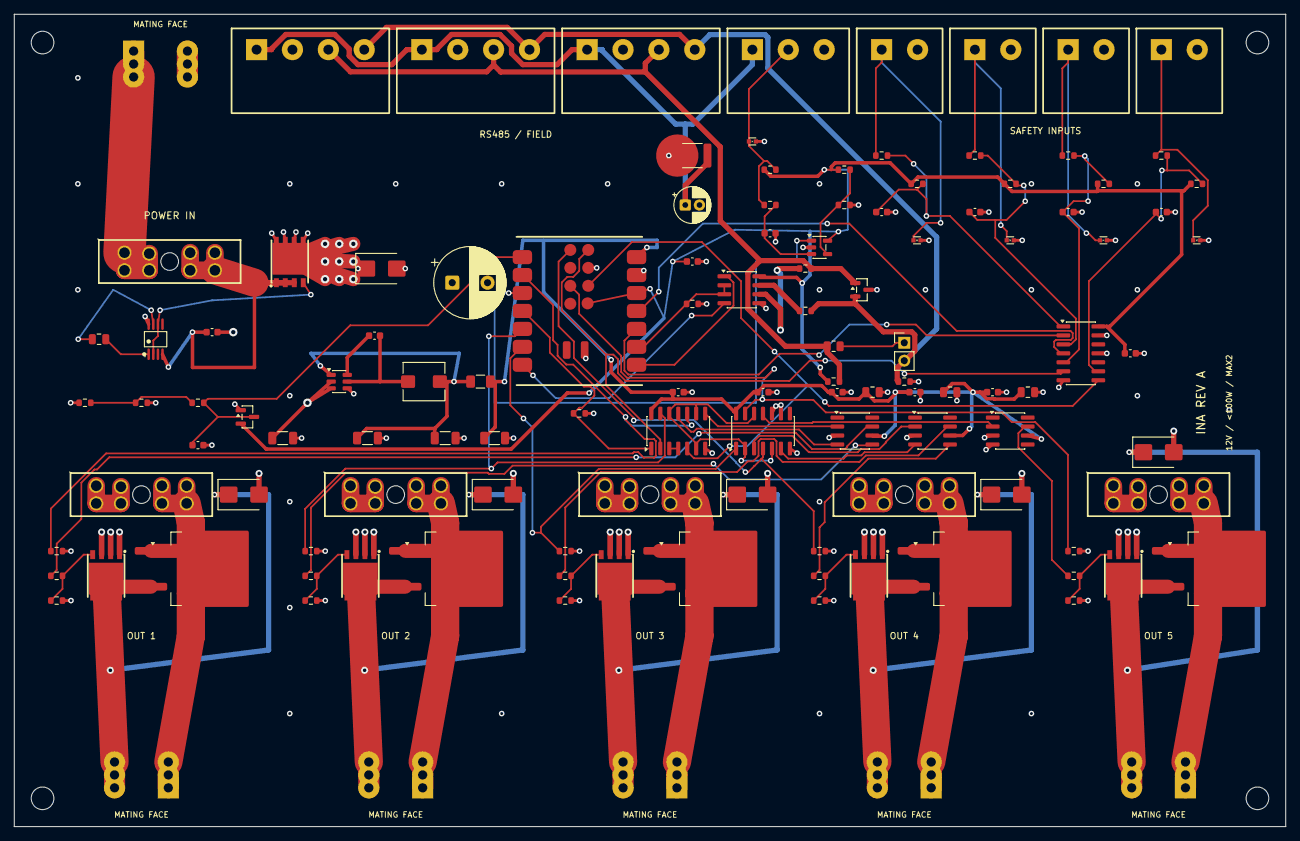
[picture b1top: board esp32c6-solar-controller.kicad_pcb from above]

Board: 4 copper layers, 180.0 x 115.0 mm, 125 parts (0 on the bottom side), 72 nets.

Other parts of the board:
H1, H2, H3, H4: M3 MOUNT; MountingHole_3.2mm_M3

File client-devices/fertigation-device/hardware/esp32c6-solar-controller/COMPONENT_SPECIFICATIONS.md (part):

# Rev A 部品仕様調査

調査日: 2026-08-01

この文書は、Rev A 回路図と発注BOMに採用した部品を、メーカーの
データシートまたはメーカー公式製品ページで照合した結果である。
同一メーカー型番・同一定数の受動部品は、設計番号をまとめて記載する。
LCSC番号は調達用識別子であり、電気仕様の根拠には使用しない。

## 1. 適用条件

- 太陽光充電器、12 Vバッテリー、BMS、バッテリー直近の主ヒューズは外付け。
- 基板入力は充電器の保護済み `LOAD` 出力。定常入力は16 V以下とする。
- MOSFET出力はすべて12 V、各負荷は100 W未満、定常電流は8.33 A未満。
- 通常は1出力だけをONにする。同時ONは最大2出力、合計200 W未満。
- センサー機種は固定しない。RS485端子は共通バス、接点端子は無電圧接点、
  流量端子はNPNオープンコレクタまたは無電圧接点を既定とする。
- 基板全体の温度範囲は、XIAO ESP32-C6、SN74HC14およびPPTCのうち最も狭い
  範囲に合わせ、暫定で `-40～+85 °C` とする。

## 2. 電源入力、逆接保護、5 V電源

| 設計番号 | 採用品 | メーカー仕様 | 回路での使用条件・判定 | 一次資料 |
|---|---|---|---|---|
| `J1` | Phoenix Contact `1720466` | PC 5/2、2極、7.62 mmピッチ、定格32 A、630 V、接触抵抗0.8 mΩ、使用温度-40～+100 °C | 基板入力最大20 Aに対して電流定格内。電線、プラグ`1718481`、圧着/締結条件も32 A相当にする | [Phoenix Contact](https://www.phoenixcontact.com/en-us/products/pcb-header-pc-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 |
| `F1`, `F10..F14` | Littelfuse `178.6165.0001` | PCB用ATOホルダ、連続22.5 A、最大30 A、32 V、UL94 V-0 | 主系統20 A、各分岐10 Aで使用可能。主系統を20 A連続で使用する場合は筐体内温度上昇を実測する | [Littelfuse](https://www.littelfuse.com/ja-jp/products/fuses-overcurrent-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 |
| `F1`挿入品 | Littelfuse `0287020.H` | ATOF、20 A、32 V、遮断容量1000 A @ 32 VDC、代表冷抵抗3.38 mΩ、代表電圧降下98 mV、代表I²t 520 A²s、推奨周囲温度上限125 °C | 2出力同時ON時の16.7 Aを許容する初期値。バッテリー側ヒューズ、配線許容電流、実測突入電流との保護協調が必要 | [ATOFデータシート](https://www.littelfuse.com/assetdocs/littelfuse_datasheet_28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 |
| `Q1`, `Q2..Q6` | TI `CSD18540Q5B` | N-MOSFET、60 V、`RDS(on)`最大2.2 mΩ @ 10 V / 3.3 mΩ @ 4.5 V、総ゲート電荷41 nC、`VGS` ±20 V、`TJ`最大175 °C | 5 Vゲート駆動に適合。出力1回路8.33 Aで25 °C規格値による導通損失は最大約0.23 W。温度上昇、銅箔、突入/拘束電流は別途実測する | [TIデータシート](https://www.ti.com/lit/ds/symlink/csd18540q5b.pdf) |
| `U13` | TI `LM74610QDGKRQ1` | 外付けN-MOSFET用逆接保護コントローラ、逆電圧-45 V、正側入力電圧の上限なし、ゲート駆動最大約5 V | 推奨範囲の2.2 µFチャージポンプ容量と100 pFアノード－カソードフィルタを実装。Q1のボディダイオード順方向電圧が起動条件を満たす | [TIデータシート](https://www.ti.com/lit/ds/symlink/lm74610-q1.pdf) |
| `C6` | Samsung `CL21B225KOFNNNE` | 2.2 µF、±10 %、16 VDC、X7R、0805、-55～+125 °C | `LM74610-Q1`の推奨220 nF～4.7 µF内。チャージポンプ両端は入力12 Vを直接受けない | [Samsung製品仕様](https://product.samsungsem.com/mlcc/CL21B225KOFNNN.do) |
| `C13` | Samsung `CL10C101JB8NNNC` | 100 pF、±5 %、50 VDC、C0G、0603 | `LM74610-Q1`データシートの入力フィルタ例と一致 | [Samsung Component Library](https://weblib.samsungsem.com/mlcc/mlcc-ec-data-sheet.do?par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 |
| `D1` | Littelfuse `SMBJ18A` | 単方向TVS、`VRWM` 18 V、`VBR` 20～22.1 V、最大クランプ29.2 V @ 20.6 A、600 W | 充電器LOADの定常最大が16 V以下の場合だけ使用。クランプ最大29.2 VはAP63205の35 V絶対最大、C1の35 V、MOSFETの60 V未満 | [Littelfuseデータシート](https://origin-savvis.littelfuse.com/~/media/electronics/dat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 |
| `C1` | Nichicon `UHE1V471MPD` | 470 µF、35 V、105 °C、10×20 mm、インピーダンス0.046 Ω @ 20 °C / 100 kHz、許容リプル1.4 Arms | 12 V入力の低周波バルク。TVS最大クランプ29.2 Vに対して約20 %の電圧余裕 | [Nichicon UHE](https://www.nichicon.co.jp/products/pdfs/uhe.pdf) |
| `U4` | Diodes Inc. `AP63205WU-7` | 固定5 V / 2 A同期整流降圧、入力推奨3.8～32 V、絶対最大35 V、1.1 MHz | 12 V系に適合。メーカー代表回路と同じ4.7 µH、10 µF入力、22 µF×2出力、100 nFブートストラップを採用 | [Diodes Inc.データシート](https://www.diodes.com/datasheet/download/AP63200-AP63201-AP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 |
| `L1` | Bourns `SRP5030TA-4R7M` | 4.7 µH ±20 %、DCR代表50 mΩ/最大53 mΩ、`Irms` 4.6 A、`Isat` 6 A、-55～+150 °C | AP63205の2 A出力とメーカー代表回路に適合 | [Bournsデータシート](https://www.bourns.com/docs/Product-Datasheets/SRP5030TA.pdf) |
| `C8` | Samsung `CL31B106KBHNNNE` | 10 µF、±10 %、50 VDC、X7R、1206 | 12 V入力デカップリング。DCバイアス後の実効容量を考慮してもAP63205の代表値を満たすか、試作時に波形確認する | [Samsung Component Library](https://weblib.samsungsem.com/mlcc/mlcc-ec-data-sheet.do?par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 |
| `C9`, `C10`, `C2` | Samsung `CL31B226KPHNNNE` | 22 µF、±10 %、10 VDC、X7R、1206 | C9/C10はAP63205出力合計44 µFで推奨22～68 µF内。C2はPTC後の5 Vロジックバルク | [Samsung Component Library](https://weblib.samsungsem.com/mlcc/mlcc-ec-data-sheet.do?par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 |
| `C7` | Samsung `CL10B104KB8NNNC` | 100 nF、±10 %、50 VDC、X7R、0603 | AP63205のBST-SW間推奨値と一致 | [Samsung製品仕様](https://product.samsungsem.com/mlcc/CL10B104KB8NNN.do) |
| `F2` | Bourns `MF-NSMF075-2` | PPTC、`Ihold` 0.75 A、`Itrip` 1.5 A、最大6 V、初期抵抗0.10 Ω以上、トリップ後最大抵抗0.40 Ω、-40～+85 °C | 5 Vロジック専用。12 Vには使用不可。XIAO、制御IC、RS485の合計電流は0.75 A未満 | [Bournsデータシート](https://www.bourns.com/docs/product-datasheets/mf-nsmf.pdf) |

## 3. コントローラ、電池電圧測定

| 設計番号 | 採用品 | メーカー仕様 | 回路での使用条件・判定 | 一次資料 |
|---|---|---|---|---|
| `U1` | Seeed Studio XIAO ESP32-C6 | 5 V入力、3.3 Vロジック、21×17.8 mm、11本の側面GPIOと4本の裏面GPIO、動作温度-40～+85 °C | 5V端子へ`5V_LOGIC`を供給し、3V3端子は小電流ロジックの出力として使用。公式24パッドSMD形状を使用 | [Seeed Studio Wiki](https://wiki.seeedstudio.com/xiao_esp32c6_getting_started/) |
| `U1`内ESP32-C6 | Espressif ESP32-C6 | GPIO4/5はストラップ端子、GPIO8/9はブートモード端子。ストラップ値はリセット時にラッチされ、その後GPIOとして使用可能 | GPIO4/5出力に47 kΩプルダウンを実装して起動時OFFを保証。00設定によりSDIOサンプリングはfalling/fallingとなる。GPIO8/9は本用途で使用しない | [Espressifデータシート](https://www.espressif.com/sites/default/files/documentation/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 |
| `R1`, `R2` | UNI-ROYAL `0603WAF1503T5E` / `0603WAF2702T5E` | 150 kΩ / 27 kΩ、±1 %、0603厚膜。0603 WAシリーズは0.1 W級 | 分圧比27/177 = 0.15254。18 V入力でADC約2.746 V、3.3 V相当の入力は約21.63 V | [UNI-ROYAL厚膜抵抗](https://www.uni-royal.cn/en/images/userfile/file/1753752986c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 |
| `R3`, `C3` | 1 kΩ + 100 nF | R: ±1 %厚膜0603、C: Samsung 100 nF X7R 50 V | ADCの電流制限とRCフィルタ。分圧器のテブナン抵抗を含む時定数は約2.4 ms | [UNI-ROYAL](https://www.uni-royal.cn/en/images/userfile/file/1753752986c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, [Samsung](https://product.samsungsem.com/mlcc/CL10B104KB8NNN.do) |
| `D3` | Nexperia `BAT54S,215` | 30 V、200 mAデュアル直列Schottky。pin 1=A1、pin 2=K2、pin 3=K1/A2共通 | pin 1=GND、pin 3=`BATT_ADC`、pin 2=3V3として上下クランプを形成 | [Nexperiaデータシート](https://assets.nexperia.com/documents/data-sheet/BAT54S.pdf) |

## 4. RS485と低電流12 Vフィールド電源

| 設計番号 | 採用品 | メーカー仕様 | 回路での使用条件・判定 | 一次資料 |
|---|---|---|---|---|
| `U3` | TI `THVD1410DR` | 3～5.5 V、最大500 kbps、バス故障保護±18 V、コモンモード±15 V、IEC ESD ±18 kV接触、開放/短絡/アイドルfail-safe、最大256ノード、-40～+125 °C | 3.3 V動作。DEと`/RE`を共通化し47 kΩで受信側へプルダウン。非絶縁バスである | [TI製品ページ](https://www.ti.com/product/THVD1410) |
| `D2` | Bourns `CDSOT23-SM712` | RS485用TVS、400 W、17 A @ 8/20 µs、IEC ESD最大±30 kV。pin 1/2が信号、pin 3が共通 | pin 1=`RS485_A`、pin 2=`RS485_B`、pin 3=GND。メーカー指定ピン接続に修正済み | [Bournsデータシート](https://bourns.com/docs/product-datasheets/cdsot23-sm712.pdf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 |
| `R10`, `R11` | UNI-ROYAL 10 Ω ±1 % | 0603、0.1 W級厚膜 | トランシーバとTVS/コネクタ間の直列ダンピング。両側合計20 Ωが終端振幅へ与える影響は実機波形で確認 | [UNI-ROYAL厚膜抵抗](https://www.uni-royal.cn/en/images/userfile/file/1753752986c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 |
| `R12`, `JP1` | 120 Ω ±1 % + Sullins `PRPC002SAAN-RC` | Rは0805厚膜、JPは2.54 mmピッチ2極ヘッダ | RS485幹線の物理終端にある基板だけ短絡プラグを装着。中間ノードでは開放 | [UNI-ROYAL厚膜抵抗](https://www.uni-royal.cn/en/images/userfile/file/1753752986c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 |
| `R13`, `R14` | 680 Ω ±1 % | 0603厚膜 | THVD1410の内部fail-safeを使うためRev AではDNP。外付けバイアスが必要な既存バスだけ評価後に実装 | [UNI-ROYAL厚膜抵抗](https://www.uni-royal.cn/en/images/userfile/file/1753752986c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 |
| `F3` | Bourns `MF-MSMF075/24-2` | PPTC、`Ihold` 0.75 A、`Itrip` 1.5 A、最大24 V / 100 A、初期抵抗0.11 Ω以上、トリップ後最大0.40 Ω | RS485センサー用12 V共通電源。3端子合計で0.75 A未満。アクチュエータ電源には使用しない | [Bournsデータシート](https://www.bourns.com/docs/product-datasheets/mf-msmf.pdf) |
| `C11` | Nichicon `UHE1E470MDD` | 47 µF、25 V、105 °C、5×11 mm、インピーダンス0.58 Ω、許容リプル210 mArms | 長いフィールド配線による低周波変動を抑える。定常16 V以下の12 Vフィールド電源に適合 | [Nichicon UHE](https://www.nichicon.co.jp/products/pdfs/uhe.pdf) |
| `J2..J4` | Phoenix Contact `1757268` | MSTBA 2.5/4、4極、5.08 mm、12 A、320 V、接触抵抗1.4 mΩ、-40～+100 °C | 12V/GND/A/B。3コネクタは電気的に同一バス。外部配線を長いスター分岐にしない | [Phoenix Contact](https://www.phoenixcontact.com/us/products/1757268/pdf) |

## 5. 流量入力、接点入力、安全ロジック

| 設計番号 | 採用品 | メーカー仕様 | 回路での使用条件・判定 | 一次資料 |
|---|---|---|---|---|
| `J5` | Phoenix Contact `1757255` | MSTBA 2.5/3、3極、5.08 mm、12 A、320 V、-40～+100 °C | 12V/パルス/GND。パルス端子は12 Vプッシュプル入力ではなくNPNオープンコレクタまたは無電圧接点用 | [Phoenix Contact](https://www.phoenixcontact.com/en-fr/products/pcb-header-mst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 |
| `U12` | TI `TLV7031DBVR` | 1.6～6.5 V、rail-to-rail入力、push-pull出力、代表消費335 nA、入力オフセット最大8 mV、内部ヒステリシス代表7 mV、代表伝搬3 µs、-40～+125 °C。DBV pin 1=OUT、2=V-、3=IN+、4=IN-、5=V+ | 3.3 V動作、比較基準1.65 V。実部品ピン番号に合わせて回路シンボルを修正済み | [TIデータシート](https://www.ti.com/lit/ds/symlink/tlv7031.pdf) |
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
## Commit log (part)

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2026-06-29 ✨ 新機能: 水やりデバイスのセンサーおよびタスク管理機能を追加
    - センサー機能を実装し、温度とTDS（総溶解固形物）を測定する機能を追加。
    - タスク管理機能を実装し、タスクのリクエストと進行状況を管理。
    - NTPサーバーとの時刻同期機能を追加し、デバイスの時間を正確に保つ。
    - 水やり機能を実装し、土壌の湿度に基づいて自動的に水を供給。
    - 各種ハードウェアインターフェース（音声、カメラ、設定、出力、土壌、TDS、温度）を追加し、デバイスの機能を拡張。
    - 設定の保存と読み込み機能を実装し、デ
2026-06-30 ✨ デバッグログ機能を追加
    - アプリケーションのデバッグログ機能を実装し、重要なイベントやエラーを記録できるようにしました。
    - 新たに `app_debug_log.h` と `app_debug_log.cpp` を作成し、ログの管理と送信を行う関数を追加しました。
    - 各モジュール（ネットワーク、ウォータリング、ランタイム設定など）での重要なイベントをログに記録するように変更しました。
    - ログの最大数やペイロードサイズなどの設定を `app_def.h` に追加しました。
    - ウォータリングの開始や完了、ネットワーク接続の状態など、アプリケー
